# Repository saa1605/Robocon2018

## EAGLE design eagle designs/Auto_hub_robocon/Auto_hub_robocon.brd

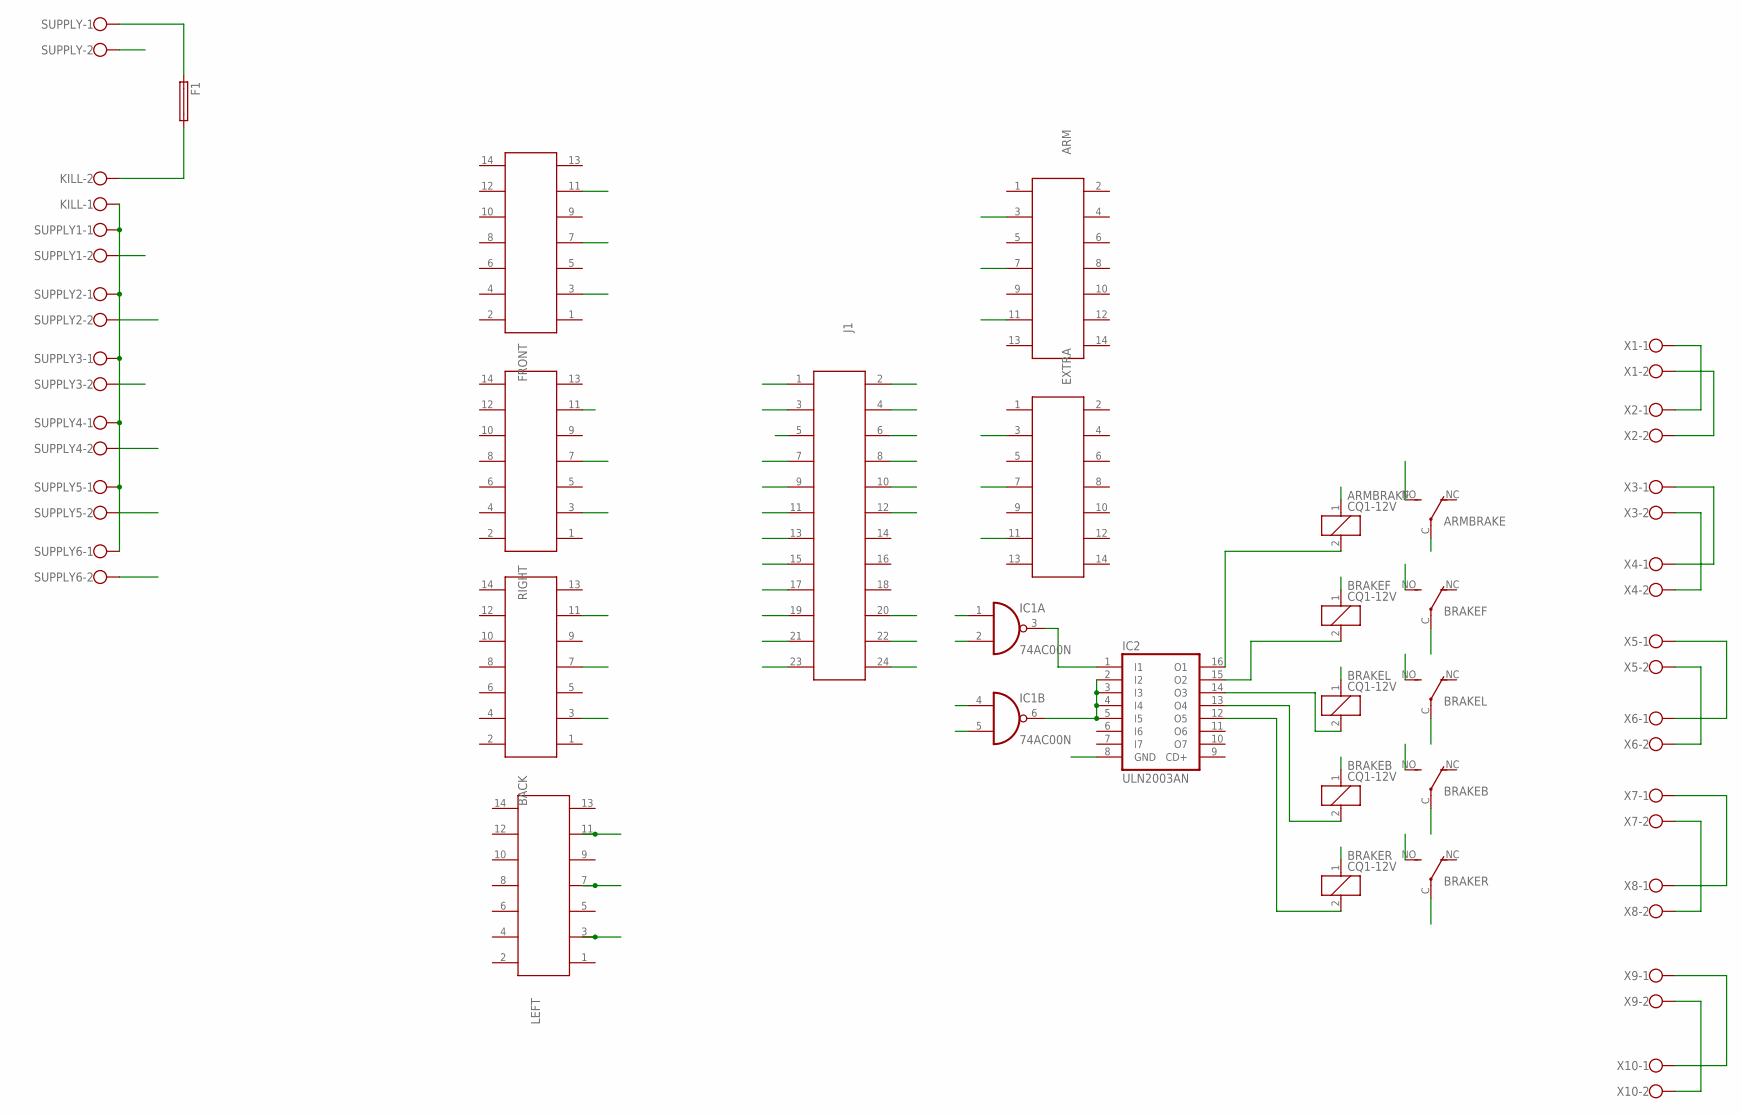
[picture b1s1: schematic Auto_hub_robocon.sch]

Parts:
ARM: 61201421621
ARMBRAKE: CQ1-12V; CQ1
BACK: 61201421621
BRAKEB: CQ1-12V; CQ1
BRAKEF: CQ1-12V; CQ1
BRAKEL: CQ1-12V; CQ1
BRAKER: CQ1-12V; CQ1
EXTRA: 61201421621
F1: GSH15
FRONT: 61201421621
IC1: 74AC00N; DIL14
IC2: ULN2003AN; DIL16
J1: 61202421621
KILL: W237-102
LEFT: 61201421621
RIGHT: 61201421621
SUPPLY, SUPPLY1, SUPPLY2, SUPPLY3, SUPPLY4, SUPPLY5, SUPPLY6: W237-102
X1, X2, X3, X4, X5, X6, X7, X8, X9, X10: W237-102

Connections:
5V: ARMBRAKE.1, BRAKEB.1, BRAKEF.1, BRAKEL.1, BRAKER.1, IC1.2 (I1), IC1.4 (I0), J1.22
ARM1: ARMBRAKE.C, X1.1, X2.1
ARM2: ARMBRAKE.NO (S), X1.2, X2.2
ARMBRAKE: IC1.1 (I0), J1.20
ARMIN1: ARM.3, J1.2
ARMIN2: ARM.11, J1.6
ARMPWM: ARM.7, J1.4
BASEBRAKE: IC1.5 (I1), J1.24
BIN1: BACK.11, J1.13
BIN2: BACK.3, J1.17
BPWM: BACK.7, J1.15
BRAKEB1: BRAKEB.C, X7.1, X8.1
BRAKEB2: BRAKEB.NO (S), X7.2, X8.2
BRAKEF1: BRAKEF.C, X3.1, X4.1
BRAKEF2: BRAKEF.NO (S), X3.2, X4.2
BRAKEL1: BRAKEL.C, X5.1, X6.1
BRAKEL2: BRAKEL.NO (S), X5.2, X6.2
BRAKER1: BRAKER.C, X9.1, X10.1
BRAKER2: BRAKER.NO (S), X9.2, X10.2
EXTRAIN1: EXTRA.3, J1.8
EXTRAIN2: EXTRA.11, J1.12
EXTRAPWM: EXTRA.7, J1.10
FIN1: FRONT.11, J1.1
FIN2: FRONT.3, J1.5
FPWM: FRONT.7, J1.3
GND: IC1.7 (GND), IC2.8 (GND), SUPPLY.2, SUPPLY1.2, SUPPLY2.2, SUPPLY3.2, SUPPLY4.2, SUPPLY5.2, SUPPLY6.2
LIN1: J1.19, LEFT.11
LIN2: J1.23, LEFT.3
LPWM: J1.21, LEFT.7
unnamed: ARMBRAKE.2, IC2.16 (O1)
unnamed: BRAKEF.2, IC2.15 (O2)
unnamed: BRAKEL.2, IC2.14 (O3)
unnamed: IC1.3 (O), IC2.1 (I1)
unnamed: BRAKEB.2, IC2.13 (O4)
unnamed: BRAKER.2, IC2.12 (O5)
unnamed: IC1.6 (O), IC2.2 (I2), IC2.3 (I3), IC2.4 (I4), IC2.5 (I5)
unnamed: F1.1, SUPPLY.1
unnamed: F1.2, KILL.2
unnamed: KILL.1, SUPPLY1.1, SUPPLY2.1, SUPPLY3.1, SUPPLY4.1, SUPPLY5.1, SUPPLY6.1
RIN1: J1.7, RIGHT.11
RIN2: J1.11, RIGHT.3
RPWM: J1.9, RIGHT.7
VCC: IC1.14 (VCC)

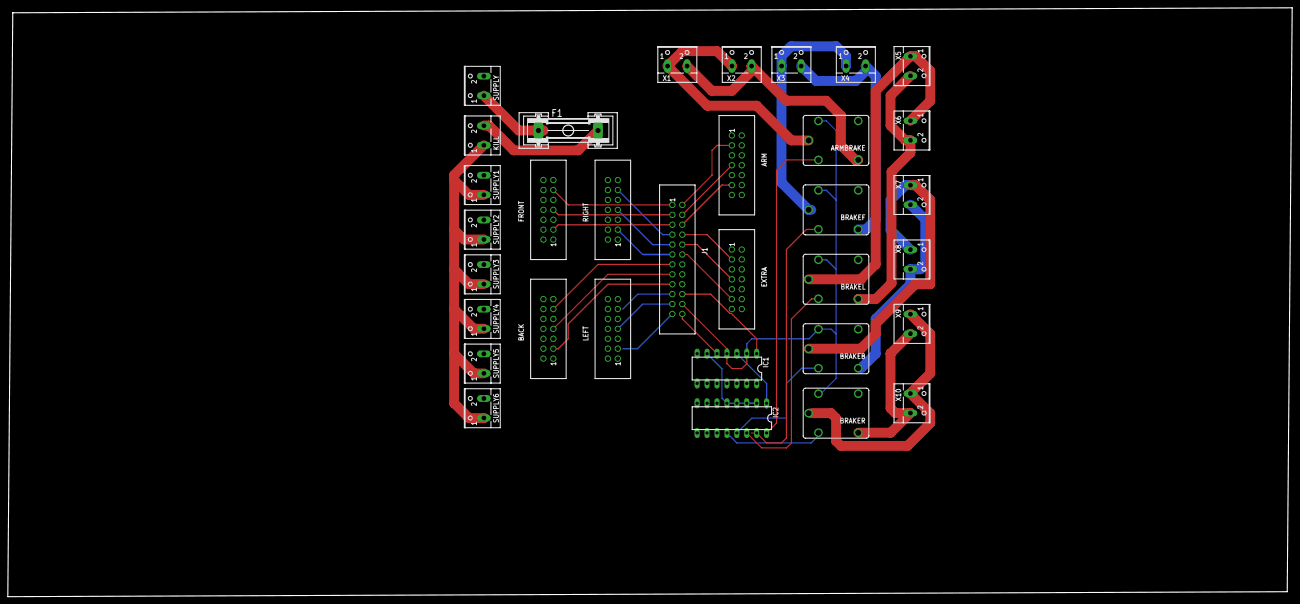
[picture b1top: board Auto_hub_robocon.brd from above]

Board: 2 copper layers, 328.9 x 150.8 mm, 33 parts (0 on the bottom side), 42 nets.

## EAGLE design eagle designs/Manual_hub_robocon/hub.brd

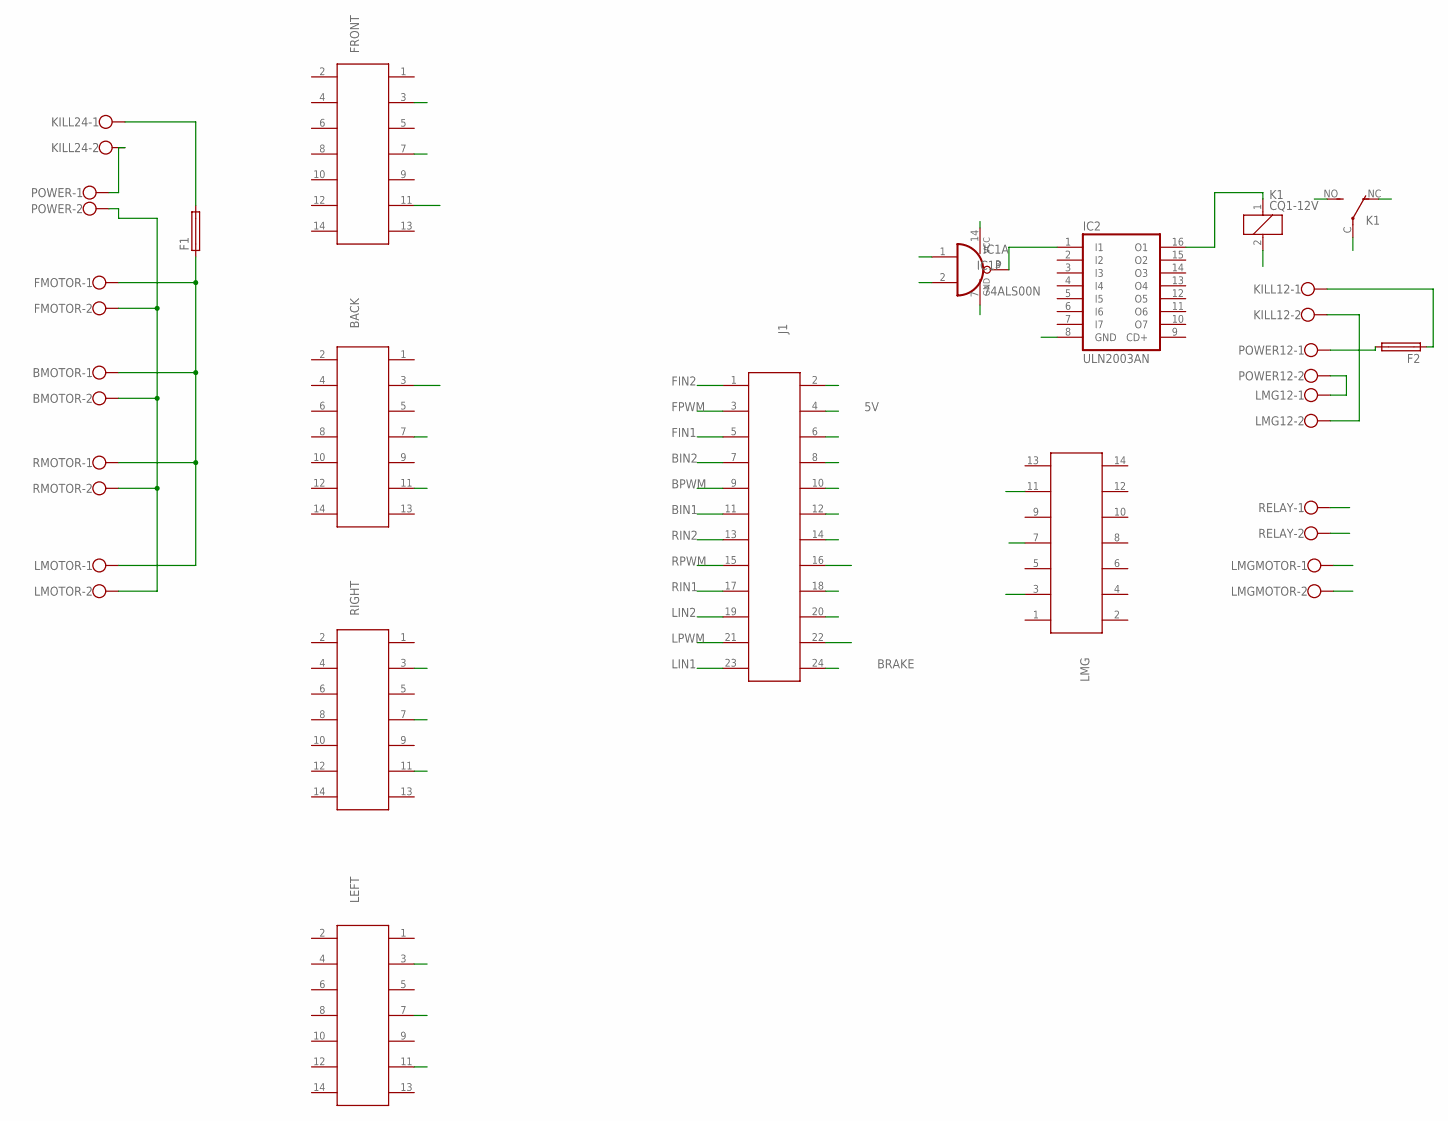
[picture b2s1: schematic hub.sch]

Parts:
BACK: 612014235121
BMOTOR: W237-102
F1, F2: GSH15
FMOTOR: W237-102
FRONT: 612014235121
IC1: 74ALS00N; DIL14
IC2: ULN2003AN; DIL16
J1: 61202421621
K1: CQ1-12V; CQ1
KILL12, KILL24: W237-102
LEFT: 612014235121
LMG: 612014235121
LMG12: W237-102
LMGMOTOR: W237-102
LMOTOR: W237-102
POWER, POWER12: W237-102
RELAY: W237-102
RIGHT: 612014235121
RMOTOR: W237-102

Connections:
5V: IC1.1 (I0), IC1.14 (VCC), J1.4, K1.2
24V: BMOTOR.1, F1.1, FMOTOR.1, LMOTOR.1, RMOTOR.1
BIN1: BACK.3, J1.11
BIN2: BACK.11, J1.7
BPWM: BACK.7, J1.9
BRAKE: IC1.2 (I1), J1.24
COM: K1.C, LMGMOTOR.2, RELAY.2
FIN1: FRONT.3, J1.5
FIN2: FRONT.11, J1.1
FPWM: FRONT.7, J1.3
GND: BMOTOR.2, FMOTOR.2, IC1.7 (GND), IC2.8 (GND), LMOTOR.2, POWER.2, RMOTOR.2
LIN1: J1.23, LEFT.3
LIN2: J1.19, LEFT.11
LMG1: J1.14, LMG.3
LMG2: J1.18, LMG.11
LMGPWM: J1.16, LMG.7
LPWM: J1.21, LEFT.7
unnamed: F1.2, KILL24.1
unnamed: IC1.3 (O), IC2.1 (I1)
unnamed: F2.2, POWER12.1
unnamed: IC2.16 (O1), K1.1
unnamed: KILL12.2, LMG12.2
unnamed: KILL24.2, POWER.1
unnamed: F2.1, KILL12.1
unnamed: LMG12.1, POWER12.2
NO: K1.NO (S), LMGMOTOR.1, RELAY.1
RIN1: J1.17, RIGHT.3
RIN2: J1.13, RIGHT.11
RPWM: J1.15, RIGHT.7

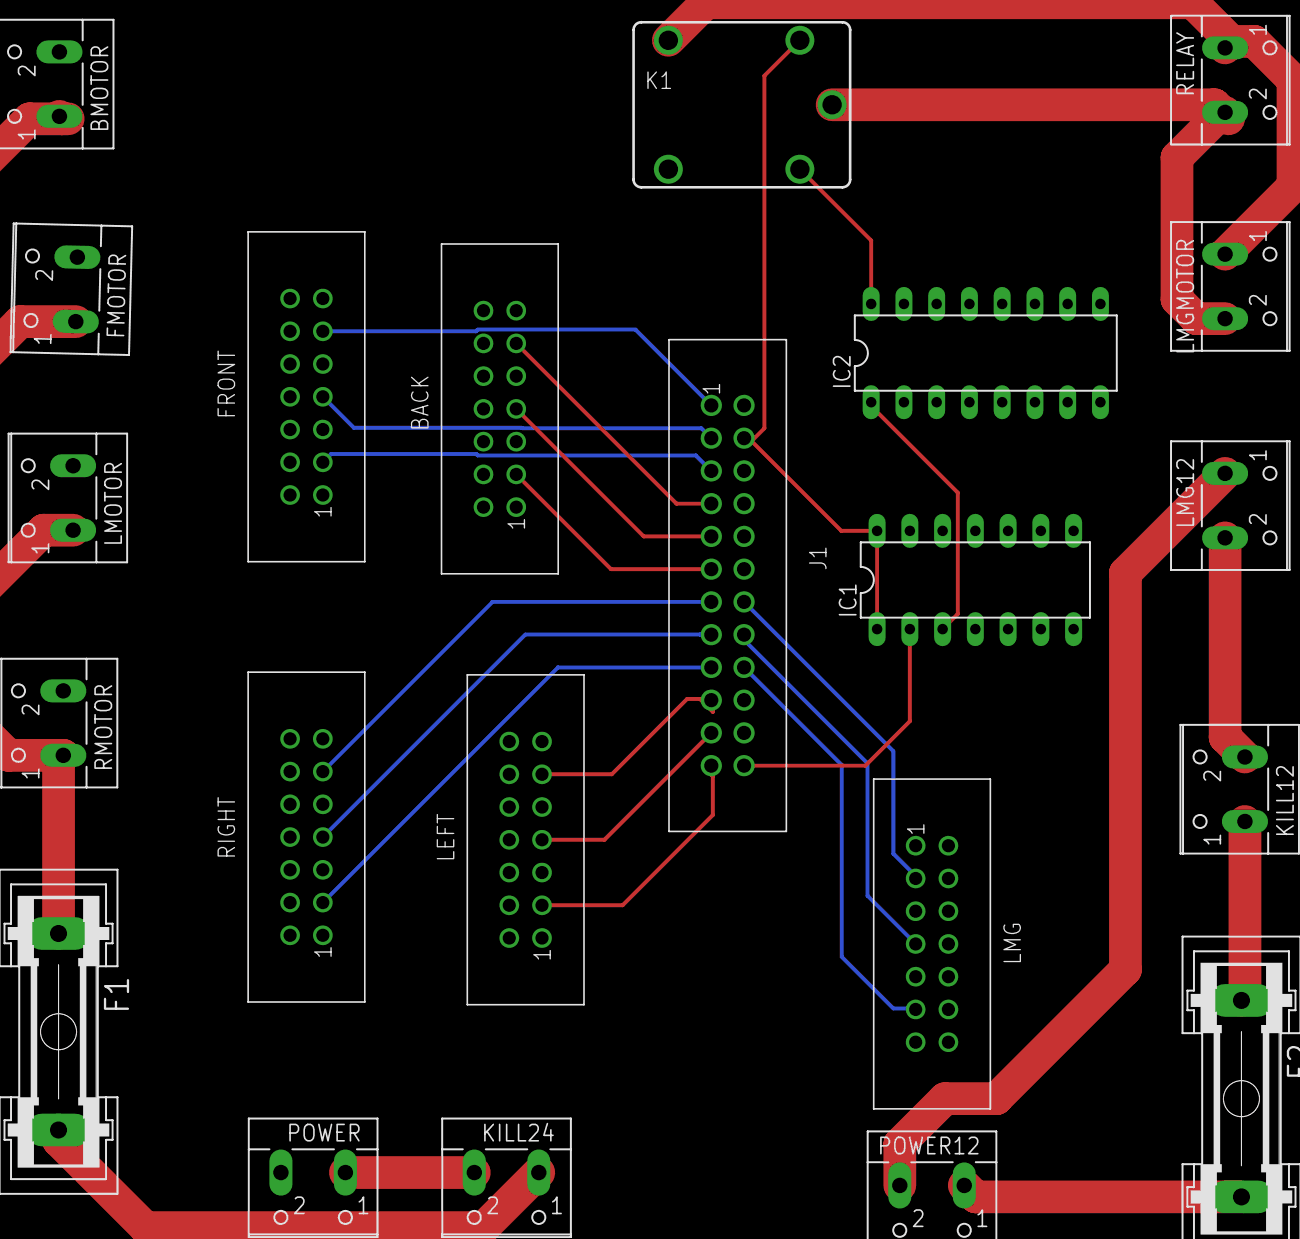
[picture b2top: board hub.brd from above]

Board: 2 copper layers, 22 parts (0 on the bottom side), 29 nets.

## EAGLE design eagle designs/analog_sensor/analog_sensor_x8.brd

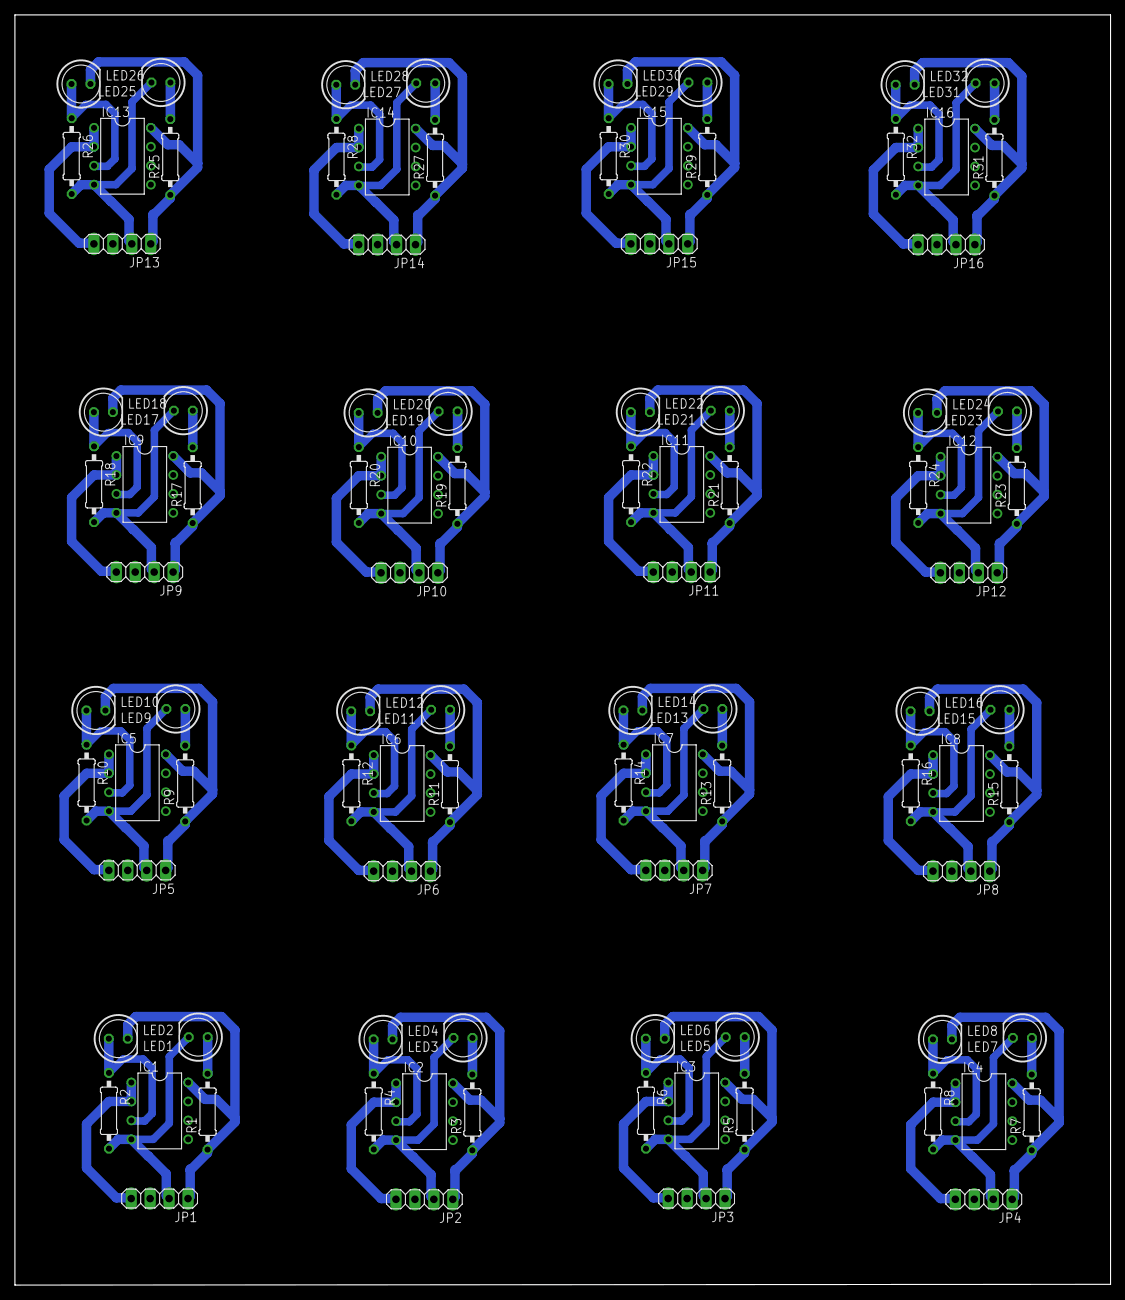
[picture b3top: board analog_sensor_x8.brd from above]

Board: 2 copper layers, 146.9 x 170.3 mm, 96 parts (0 on the bottom side), 80 nets.

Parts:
IC1, IC2, IC3, IC4, IC5, IC6, IC7, IC8, IC9, IC10, IC11, IC12, IC13, IC14, IC15, IC16: LM358N; DIL08
JP1, JP2, JP3, JP4, JP5, JP6, JP7, JP8, JP9, JP10, JP11, JP12, JP13, JP14, JP15, JP16: 1X04
LED1, LED2, LED3, LED4, LED5, LED6, LED7, LED8, LED9, LED10, LED11, LED12, LED13, LED14, LED15, LED16, LED17, LED18, LED19, LED20, LED21, LED22, LED23, LED24, LED25, LED26, LED27, LED28, LED29, LED30, LED31, LED32: LED5MM
R1, R2, R3, R4, R5, R6, R7, R8, R9, R10, R11, R12, R13, R14, R15, R16, R17, R18, R19, R20, R21, R22, R23, R24, R25, R26, R27, R28, R29, R30, R31, R32: 0207/10

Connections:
GND: IC1.4, JP1.2, LED1.K, R2.2
GND1: IC2.4, JP2.2, LED3.K, R4.2
GND2: IC3.4, JP3.2, LED5.K, R6.2
GND3: IC4.4, JP4.2, LED7.K, R8.2
GND4: IC5.4, JP5.2, LED9.K, R10.2
GND5: IC6.4, JP6.2, LED11.K, R12.2
GND6: IC7.4, JP7.2, LED13.K, R14.2
GND7: IC8.4, JP8.2, LED15.K, R16.2
GND8: IC9.4, JP9.2, LED17.K, R18.2
GND9: IC10.4, JP10.2, LED19.K, R20.2
GND10: IC11.4, JP11.2, LED21.K, R22.2
GND11: IC12.4, JP12.2, LED23.K, R24.2
GND12: IC13.4, JP13.2, LED25.K, R26.2
GND13: IC14.4, JP14.2, LED27.K, R28.2
GND14: IC15.4, JP15.2, LED29.K, R30.2
GND15: IC16.4, JP16.2, LED31.K, R32.2
unnamed: IC1.3, LED2.A, R2.1
unnamed: IC2.3, LED4.A, R4.1
unnamed: LED1.A, R1.2
unnamed: LED3.A, R3.2
unnamed: IC3.3, LED6.A, R6.1
unnamed: LED5.A, R5.2
unnamed: IC4.3, LED8.A, R8.1
unnamed: LED7.A, R7.2
unnamed: IC5.3, LED10.A, R10.1
unnamed: LED9.A, R9.2
unnamed: IC6.3, LED12.A, R12.1
unnamed: LED11.A, R11.2
unnamed: IC7.3, LED14.A, R14.1
unnamed: LED13.A, R13.2
unnamed: IC8.3, LED16.A, R16.1
unnamed: LED15.A, R15.2
unnamed: IC9.3, LED18.A, R18.1
unnamed: LED17.A, R17.2
unnamed: IC10.3, LED20.A, R20.1
unnamed: LED19.A, R19.2
unnamed: IC11.3, LED22.A, R22.1
unnamed: LED21.A, R21.2
unnamed: IC12.3, LED24.A, R24.1
unnamed: LED23.A, R23.2
unnamed: IC13.3, LED26.A, R26.1
unnamed: LED25.A, R25.2
unnamed: IC14.3, LED28.A, R28.1
unnamed: LED27.A, R27.2
unnamed: IC15.3, LED30.A, R30.1
unnamed: LED29.A, R29.2
unnamed: IC16.3, LED32.A, R32.1
unnamed: LED31.A, R31.2
SIGNAL: IC1.1, IC1.2, JP1.4
SIGNAL1: IC2.1, IC2.2, JP2.4
SIGNAL2: IC3.1, IC3.2, JP3.4
SIGNAL3: IC4.1, IC4.2, JP4.4
SIGNAL4: IC5.1, IC5.2, JP5.4
SIGNAL5: IC6.1, IC6.2, JP6.4
SIGNAL6: IC7.1, IC7.2, JP7.4
SIGNAL7: IC8.1, IC8.2, JP8.4
SIGNAL8: IC9.1, IC9.2, JP9.4
SIGNAL9: IC10.1, IC10.2, JP10.4
SIGNAL10: IC11.1, IC11.2, JP11.4
SIGNAL11: IC12.1, IC12.2, JP12.4
SIGNAL12: IC13.1, IC13.2, JP13.4
SIGNAL13: IC14.1, IC14.2, JP14.4
SIGNAL14: IC15.1, IC15.2, JP15.4
SIGNAL15: IC16.1, IC16.2, JP16.4
VCC: IC1.8, JP1.1, LED2.K, R1.1
VCC1: IC2.8, JP2.1, LED4.K, R3.1
VCC2: IC3.8, JP3.1, LED6.K, R5.1
VCC3: IC4.8, JP4.1, LED8.K, R7.1
VCC4: IC5.8, JP5.1, LED10.K, R9.1
VCC5: IC6.8, JP6.1, LED12.K, R11.1
VCC6: IC7.8, JP7.1, LED14.K, R13.1
VCC7: IC8.8, JP8.1, LED16.K, R15.1
VCC8: IC9.8, JP9.1, LED18.K, R17.1
VCC9: IC10.8, JP10.1, LED20.K, R19.1
VCC10: IC11.8, JP11.1, LED22.K, R21.1
VCC11: IC12.8, JP12.1, LED24.K, R23.1
VCC12: IC13.8, JP13.1, LED26.K, R25.1
VCC13: IC14.8, JP14.1, LED28.K, R27.1
VCC14: IC15.8, JP15.1, LED30.K, R29.1
VCC15: IC16.8, JP16.1, LED32.K, R31.1

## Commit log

2017-11-06 All files classified in folders
2017-11-07 Changes in catapult test
2017-12-18 Added sensorReadings header file
2017-12-18 Ready Modules
2017-12-18 changed getPosition funtion name
    changed name of getPosition() to get_line_position();
2017-12-19 Manual bot testing added
2017-12-19 Added Draft 2
2017-12-19 Added new folder for manual bot codes
2017-12-19 Added Encoder Readings
2017-12-19 EncoderReadings.h completed
2017-12-19 Functions for 2 8-Sensors Arrays added in SensorsReadings.h
2017-12-19 Folder moved
2017-12-19 Created seperate folder for Adc and Digital and made some variables of Draft_Adc's header files local
2017-12-20 Added codes for piston andbump switch and libraries folder
2017-12-20 changes to manual codes
2017-12-21 Manual bot alignment code added
2017-12-22 Added pixy code and created different folder for line following and transfer codes
2017-12-22 converted variables of digital header libs from global to local and added mapEverythingToDarkGreen() in SensorReadings.h of Adc and digitaliseReadings() in SensorReadings.h of Digital
2017-12-22 Added eagle file for hub
2017-12-23 Sensor PCB added
2017-12-23 map function
2017-12-23 changes to eagle schematics
2017-12-23 Sensorboard added in eagle design
2017-12-30 for educational purposes
2018-01-02 Added controller disconnected error
2018-01-02 Draft3 Digital Tuning added
2018-01-02 Added Draft3 Digital Tuning and Computation of angle from 2 arucos
2018-01-03 PS3 USB library and sample code
2018-01-03 draft3 tuning checked only sensors
2018-01-03 added Readme for chindi debugs which took too much time to resolve
2018-01-04 Added pinsDefAuto
2018-01-04 Draft3_Digital_Tuning #Day1
2018-01-05 Added seperate pids for rotational and translational line
2018-01-05 toggle pid Flag
2018-01-11 Added Latest pinsDefAuto and Added Draft4 and Draft5 both with front and back added
2018-01-12 Front back changes
2018-01-12 Draft 5 junction algo
2018-01-15 Added code with slow flag and aruco
2018-01-15 first turn tested
2018-01-16 First Junctio tested
2018-01-20 Added encoder ticks code for 128 change initialization if changing pins
2018-02-06 updated the pinDefsAuto
2018-02-06 nochanges
2018-02-06 Working Code
2018-02-06 updated pinDefsAuto
2018-02-06 30th jan throws
2018-08-30 Added all codes used in pune at robocon

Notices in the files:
parts and their libraries:
Wurth_Elektronik_Electromechanic_Wire_to: Copyright: Würth Elektronik
